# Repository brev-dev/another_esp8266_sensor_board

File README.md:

# Another ESP8266 Sensor Board

This repo contains build instructions for a multi-purpose esp8266 sensor device for home IoT projects. 

*Board V5, partially populated. Image generated in KiCad.*

## Contents

- [Introduction](https://github.com/brev-dev/another_esp8266_sensor_board#introduction)
  - [Example devices](https://github.com/brev-dev/another_esp8266_sensor_board#example-devices)
  - [Why use this board?](https://github.com/brev-dev/another_esp8266_sensor_board#why-use-this-board-and-not-insert-off-the-shelf-microcontroller-board-here)
- [Component discussion](https://github.com/brev-dev/another_esp8266_sensor_board#component-discussion)
  - [Power](https://github.com/brev-dev/another_esp8266_sensor_board#power)
  - [LDO regulator](https://github.com/brev-dev/another_esp8266_sensor_board#ldo-regulator)
  - [Electrical Noise](https://github.com/brev-dev/another_esp8266_sensor_board#electrical-noise)
  - [ESP8266](https://github.com/brev-dev/another_esp8266_sensor_board#esp8266)
  - [Voltage supervisor](https://github.com/brev-dev/another_esp8266_sensor_board#voltage-supervisor-optional-with-jumper-jp1)
  - [LORA module](https://github.com/brev-dev/another_esp8266_sensor_board#lora-rfwm95w-module)
  - [ADC connections](https://github.com/brev-dev/another_esp8266_sensor_board#adc-connections)
  - [Water pump, and connector](https://github.com/brev-dev/another_esp8266_sensor_board#water-pump-and-connector)
  - [Enclosure](https://github.com/brev-dev/another_esp8266_sensor_board#enclosure)
  - [Sensors](https://github.com/brev-dev/another_esp8266_sensor_board#sensors)
    - [Temperature, humidity, pressure (BME280)](https://github.com/brev-dev/another_esp8266_sensor_board#temperature-humidity-pressure-bme280)
    - [Lux (BH1750)](https://github.com/brev-dev/another_esp8266_sensor_board#lux-bh1750)
    - [CO<sub>2</sub> (MH-Z19C)](https://github.com/brev-dev/another_esp8266_sensor_board#co2-mh-z19c)
    - [Moisture](https://github.com/brev-dev/another_esp8266_sensor_board#moisture)
- [Design & fabrication](https://github.com/brev-dev/another_esp8266_sensor_board#design--fabrication)
- [Software](https://github.com/brev-dev/another_esp8266_sensor_board#software)
  - [Tasmota](https://github.com/brev-dev/another_esp8266_sensor_board#tasmota)
  - [Micropython](https://github.com/brev-dev/another_esp8266_sensor_board#micropython)
- [Home IOT setup](https://github.com/brev-dev/another_esp8266_sensor_board#home-iot-setup)
- [ToDo](https://github.com/brev-dev/another_esp8266_sensor_board#todo-could-be-done-not-necessarily-will-be-done)

## Introduction

This sensor board meets most of my home-automation hardware needs. It fits in a [cheap, widely-available enclosure](https://github.com/brev-dev/another_esp8266_sensor_board/blob/f84a305c095048d2f336beb286c9c32f08003d64/images/project_box.jpg) (no 3d printing required), and can be powered either by a Li-Ion battery (voltage-monitoring, charging, reverse-polarity, and protection circuitry included) or USB, with appropriate power sharing if the USB and battery are connected simultaneously. On the software side, I’ve kept things as high-level as possible: Tasmota for most usage scenarios; micropython where needed. Communication utilizes the MQTT protocol over Wi-Fi, or LORA (I use the board as both a [remote LORA sensor, and as a LORA-MQTT bridge](https://github.com/brev-dev/LORA_esp8266_sensor_MQTT_bridge/)).

The board is designed for the following [sensors](https://github.com/brev-dev/another_esp8266_sensor_board#sensors), as well as motor/pump control (for automatic plant watering). GPIO pins remain easily-accessible, so this board can also be used as the basis for many other sensors.

- [Temperature/Humidity/Pressure (BME280)](https://github.com/brev-dev/another_esp8266_sensor_board#temperaturehumiditypressure-bme280)
- [Lux (BH1750)](https://github.com/brev-dev/another_esp8266_sensor_board#lux-bh1750)
- [CO<sub>2</sub> (MH-Z19C)](https://github.com/brev-dev/another_esp8266_sensor_board#co2-mh-z19c)
- [Moisture](https://github.com/brev-dev/another_esp8266_sensor_board#moisture)

The use of an esp8266 comes with some limitations, specifically around available GPIO, and only one ADC port. This means that not all potential functionality is available at the same time. Yes, these limitations could be overcome either with a port splitter, or by utilizing a different microcontroller such as an ESP32; however part of the fun for me was seeing how much I could do with only the esp8266, and the end result fits all of my use-cases.

### Example devices

|  |  |
| --- | --- |
| *V4, with BME280 (temperature, pressure and humidity), BH1750 (lux) and moisture (via the audio plug) sensors. Equipped for watering pump (bottom right); not currently connected.* | *V5, with the BME280 and MH-Z19C (CO<sub>2</sub>) sensors* |

|  |
| --- |
| *A fresh delivery of V5 boards* |

### Why use this board, and not *\*insert-off-the-shelf-microcontroller-board-here\**?
You could (should?!) use something else. I initially designed this as a way to learn about IoT sensors and circuit design/fabrication. I’ve stuck with it because it provides several advantages over off-the-shelf boards:
1.	Convenient project-box fit without 3D printing
2.	No tangle of wires: most sensors are directly mounted to the board
3.	Theoretically better protection & stability (control over noise-suppression features, battery polarity protection, and voltage supervision). Of course, in practice this benefit is probably more than outweighed by my lack of board-design experience.

## Component Discussion

### Power

The board can be powered either directly from USB, or from a Li-Ion battery. Board V4 and earlier used micro-USB; V5 uses USB-C. The cutout on the left of the board is designed to accommodate a 1-cell 18650-battery case such as [this](https://github.com/brev-dev/another_esp8266_sensor_board/blob/980b60a9790c6bc3b052b28f8b95426f12ae9da2/images/18650_battery_case.jpg) ([purchase link](https://www.aliexpress.com/item/32993737904.html)). The battery connector is a 2-pin JST-PH (2mm pitch), but if you prefer, just solder the wires directly to the connectors.

If both battery and USB are connected simultaneously, a power-sharing circuit ensures that only the USB powers the board.
The battery is used in conjunction with a copy of the common 3-chip TP4056-based module for charging. There’s a switch provided if you’re not using a battery and want to bypass this circuitry (or if you don't want the battery to charge while USB is connected). The module includes protection for overcharge, over-discharge, overcurrent and short-circuit. Note that the overcurrent and short-circuit protection is bypassed for the rest of the board (not the battery) when USB is connected, and the power-sharing circuit is therefore active. 
The standard charging module doesn’t include battery-polarity protection, so I’ve also added that.

Battery voltage monitoring is available when either jumper JP5 (front) or JP6 (back) is bridged. This connects the positive battery terminal, through a voltage divider, to the esp's sole ADC pin. This connection is optional because the moisture sensor (and of course other sensors) also need access to the ADC. Due to this, it's clearly not possible to monitor both battery voltage and a soil moisture sensor at the same time with the V5 board.

*Notes*
- The FS8205 dual MOSFET chip comes in two package sizes. I chose the (slightly less common) SOT-23-6 variant because it's easier to hand-solder.
- Be aware that some AliExpress vendors are (I suspect accidentally) selling me4056 chips as tp4056. This chip has the same purpose but different pinout, so it won't work on the board. [Here's](https://github.com/brev-dev/another_esp8266_sensor_board/blob/a93f9e18d06ddcca5e1f6364de4ef48cf533c392/images/me4056.jpg) a bag of me4056's I received from one vendor (and was given a full refund when I finally worked-out what the problem was).
- As my 3-chip TP4056 charger footprint remains consistent with the widely-available modules, if you have one of those handy you can simply piggy-back it, rather than adding components directly to the board. [Here's](https://github.com/brev-dev/another_esp8266_sensor_board/blob/f170df5e5ed5a01450a450957b2c13060da18a92/images/tp4056_piggyback.jpg) an older example where I piggy-backed the charger circuit: just join the 6 corner pads. Note that the pictured module also comes with the alternative 8205A MOSFET package.
- I chose USB sockets that were as easy to hand-solder as possible, noting that only the power, not data, connectors are needed. For micro-USB you can find a [2-pin socket](https://github.com/brev-dev/another_esp8266_sensor_board/blob/e99d01fb7cc91dd79cf12d4cf2d8f64e2b0c8e33/datasheets/microUSB_socket_2pin.jpg) ([purchase link](https://www.aliexpress.com/item/33039304643.html)). I haven't found an equivalent for USB-C, but [this](https://github.com/brev-dev/another_esp8266_sensor_board/blob/e99d01fb7cc91dd79cf12d4cf2d8f64e2b0c8e33/datasheets/usbc_socket_6pin.webp) socket ([purchase link](https://www.aliexpress.com/item/4000011358933.html)) offers a smaller number of connectors (enough for USB2 data as well as power, I believe).
- If you only need a minimal USB-powered board, you can skip all of the charging, power sharing and reverse polarity components. Just add a USB socket (or connect directly to pads H5 (+5v) and H6 (ground), and bridge the two pads on diode footprint D2.

### LDO regulator

There’s a dizzying range of possible LDO ICs to choose from. I settled on the XC6203P332PR due to its relatively high current output, and low dropout voltage. Board V4 had footprints for two alternative regulators, which I was planning to test for stability, but these weren’t needed and were removed in V5. 
#### Tantalum capacitors
On PCB version 4 I paired two 1μF tantalum capacitors with the XC6203, per the [datasheet](https://github.com/brev-dev/another_esp8266_sensor_board/blob/86c8875968cf48237dee9fcda43d4448a1e4a00b/datasheets/XC6203.pdf). I had a capacitor fail on two of these boards after a few weeks of use, causing a short-circuit and lots of smoke (the boards were being USB-powered at the time). After reading tantalum horror-stories online, I decided to experiment with swapping them for ceramics on V5, and have experienced no further problems. I later discovered that the two failures were my fault: I fitted the parts in reverse! I’m sure there’s a good reason why the polarity-marker band on tantalums denotes the positive, while on aluminium capacitors and diodes it denotes the negative, but they tripped-up this newbie.

#### An aside: Cheap ESP-12F adaptor boards

Conveniently, the XC6203P332PR is also compatible with the[ white ESP-12F adaptor boards](https://github.com/brev-dev/another_esp8266_sensor_board/blob/0b8a2c9c500916e484b68a6f7c3c33d089ebb65e/images/esp-12f%20white%20adapter.jpg). It’s smaller than the provided footprint, but can still be soldered onto it with little trouble. Make sure you remove the central zero-ohm resistor on the front of the board if using a board-mounted regulator.

### Electrical Noise

I learned the hard way about the electrical-noise sensitivity of the ESP8266: on V3 of the board, it would reboot whenever the watering motor was activated. I overcame this in V4 with component repositioning (moving the motor to the far end away from the microcontroller), adding extra capacitors next to the motor connection, increasing power trace width vs signal traces, minimizing loops on the ground plane, and separating the motor ground-plane return path from the rest of the components.

### ESP8266
The board is designed for an ESP-12F. I tend to flash the chip in a [programmer board](https://github.com/brev-dev/another_esp8266_sensor_board/blob/0b8a2c9c500916e484b68a6f7c3c33d089ebb65e/images/esp-12f%20programmer.jpg) prior to soldering it on, just to check it's working.

When installed, it can be flashed in the normal way by connecting a USB-UART interface board to the appropriate pins.

#### Connection summary

| Pin# | Port | Board Connection | Resistor\* | 
| --- | --- | --- | --- | 
| 1 | RST | Reset button |  |
| 2 | ADC | ADC (moisture or battery)|  |
| 3 | EN | Chip enable | Supervisor, or E-PU |
| 4 | IO16 | DeepSleep |  |
| 5 | IO14 | I2C SCL, or SPI SCK |  |
| 6 | IO12 | Moisture VCC, or SPI SDO-MISO |  |
| 7 | IO13 | I2C SDA, or SPI MOSI |  |
| 8 | VCC |  |  | VCC |  |
| 15 | GND |  |  | GND |  |
| 16 | IO15 | LORA NSS | E-PD |
| 17 | IO2 | Onboard LED, & SPI SS |  |
| 18 | IO0 | Flash button | E-PU |
| 19 | IO4 | Mode switch (GND: use sleep) | E-PU |
| 20 | IO5 | Water pump, or LORA DIO | E-PD |
| 21 | RXD | CO<sub>2</sub> Tx |  |
| 22 | TXD | CO<sub>2</sub> Rx |  |

\* Resistor attached to pin: I:Internal, E:External, PU:Pull-Up, PD:Pull-Down

#### Deep sleep (optional with jumper JP2)

There seems to be some online [debates](https://www.esp8266.com/viewtopic.php?f=160&t=13625) about the optimal way to connect RST to GPIO16 in order to use the ESP8266’s DeepSleep functionality. I’ve erred on the side of caution and added a diode between the two.

### Voltage supervisor (optional with jumper JP1)

The ESP8266 is susceptible to brown-outs if the voltage is too low (a good explanation of this problem can be found [here](https://youtu.be/cKDv0aN67BY)). In conjunction with the non-instantaneous increase in voltage from the regulator when power is first applied, this can lead to boot problems. To protect against this, I’ve included an optional voltage supervisor ([TPS3839G33DBZ](https://github.com/brev-dev/another_esp8266_sensor_board/blob/4a8da56aba7b092c4e5784e14ad378a6c07b094b/datasheets/tps3839.pdf)) which will only set the chip-enable pin high when voltage is above an appropriate threshold. 
However, I’ve yet to notice brown-outs being a problem, so I sometimes skip this component.

### LORA (RFWM95W) module

*A pair of LORA-equipped devices in their enclosures*

Combining an esp8266 with a LORA module is a stretch when it comes to available gpio. This board is designed to work with SX1276 LORA modules ([example link](https://www.aliexpress.com/item/32984655636.html)), and leans heavily on the design from [here](https://github.com/hallard/WeMos-Lora), which minimizes needed ports by linking three of the LORA module's pins (DIO0, 1 and 2) to one esp8266 pin via three diodes (board footprints D9, D10 and D11 respectively). This DIO-sharing configuration needs special handling in software. However, for simple LORA communications only DIO0 is needed, so for my LORA boards to date I have bridged D9, and left D10 and D11 disconnected.

#### Antenna
For testing, you can directly solder the common helical-wire antennas (often included with the purchase of a module) directly to the module's antenna pin. Range will suck, though. For better range attach a higher-gain antenna (I use 5dbi antennas bought [here](https://www.aliexpress.com/item/32979875502.html)). I include an IPEX U.FL-R footprint at AE1. Alternatively, SMA edge-mounted connectors fit nicely on the edge of the board over footprint J5. These can be wired-up as follows (this example is using board V4, but the same will work for V5): [top](https://github.com/brev-dev/another_esp8266_sensor_board/blob/493c38c68af71970a35fda9a3fc562d0f8774722/images/antenna_top.jpg) and [bottom](https://github.com/brev-dev/another_esp8266_sensor_board/blob/493c38c68af71970a35fda9a3fc562d0f8774722/images/antenna_bottom.jpg).

*Notes*
- Remember to install capacitor C10 if you're adding a LORA module to the board.

### ADC Connections

A single ADC is available on the esp8266, with a measurement range from 0V to 1V. For measuring higher voltages, a [voltage divider](https://ohmslawcalculator.com/voltage-divider-calculator) is therefore needed. On board V5, the ADC can either be used for peripherals connected to the audio jack, or to monitor the battery voltage if either JP11 or JP5 is closed.

Connections via the audio jack go through a divider with R1=470 kΩ (component R7), R2=200 kΩ (component R8). This permits measurement of voltages up to 3.3V (3.3V is lowered to approximately 0.985V; calibrate the signal for higher accuracy).

The battery connection adds an additional 330 kΩ (component R10) resistor in series with component R7, leading to R1=800 kΩ. This increases the measurement range up to 5V.

#### The audio-style socket
I chose to use a 4-pole audio jack (model PJ313E) to connect the moisture sensors to the board. For now, only three of the four poles are connected; the fourth is a spare with an eye to future functionality. Starting from the base to the tip of the audio plug, the current connections are:

| Pole | Connection |
| --- | --- |
| 1 | GND |
| 2 | No connection |
| 3 | 3.3V (from GPIO12, via JP3) |
| 4 | To ADC via 3.3V voltage divider |

I've experienced one problem with my chosen socket (or maybe the combination of the socket and the plugs I use): by default, it's failing to make a connection to all four poles. This can be seen in the top image [here](https://github.com/brev-dev/another_esp8266_sensor_board/blob/e8318408b542502163760f25e8133f11a53af489/images/audio_socket_mod.jpg), where the deepest contact-pin (Pole 4) isn't deflected. To fix the problem, I snipped/filed-off the protruding plastic front part of the socket ([bottom image](https://github.com/brev-dev/another_esp8266_sensor_board/blob/e8318408b542502163760f25e8133f11a53af489/images/audio_socket_mod.jpg))

### Water pump, and connector
Small water pumps and the necessary flexible tubing are widely available. As discussed [above](https://github.com/brev-dev/another_esp8266_sensor_board/blob/main/README.md#electrical-noise), they're electrically-noisy buggers; hence why the connector for the pump is in the far corner of the board from the esp, and shielded behind two capacitors of its own. It's normally powered by gpio5, via an N-channel MOSFET, or can be manually operated with the optional button SW5.

For simplicity, and since the small pumps seem to be able to function over quite a wide voltage range, the pump is supplied with whatever voltage is currently powering the board (defined by the state of the power sharing circuitry): if USB is connected, it'll be 5V minus the forward voltage across diodes D2 and D8; if battery-powered, it'll be the battery voltage minus the D8 drop. In practice it really doesn't make much difference: slightly more water will be pumped during a given time when on USB vs battery-powered.

For the pump's board connection, there's a footprint for a DC-002 socket. I considered using a USB socket but decided that was misleading since the output voltage isn't always the 5V that one would expect from USB. On the board pictured above, I skipped the power-jack socket and simply connected a double pin-header socket instead.

### Enclosure

I chose [this project box](https://github.com/brev-dev/another_esp8266_sensor_board/blob/f84a305c095048d2f336beb286c9c32f08003d64/images/project_box.jpg) because it's cheap, widely-available, and just the right size for the pcb and an 18650 battery.

8mm M2.6 screws are needed to attach the board to the box, such as [these](https://www.aliexpress.com/item/4000108693024.html).

### Sensors

| Property | Module | Board Connection | Datasheet | Purchase Link\*|
| ---| --- | --- | :---: | --- |
| Temperature, pressure, humidity | BME280 | Direct (2.54mm headers) | [Link](https://github.com/brev-dev/another_esp8266_sensor_board/blob/e3f53c214705e32eaa9f90e711b66ee1d1c71691/datasheets/BST-BME280_DS001-11-844833.pdf) | |
|	Lux | BH1750 | Direct (2.00mm headers) | [Link](https://github.com/brev-dev/another_esp8266_sensor_board/blob/d842e8ac7ead9bd1a256e17d498e4c6692d75f80/datasheets/BH1750FVI.pdf) | [AliExpress](https://www.aliexpress.com/item/32983784786.html) |
|	CO<sub>2</sub> | MH-Z19C | Direct (2.54mm headers) | [Link](https://github.com/brev-dev/another_esp8266_sensor_board/blob/55dd2d41b445c80636574d447e5fac080cfa47e3/datasheets/mh-z19c-pins-type-co2-manual-ver1_0.pdf) | [AliExpress](https://www.aliexpress.com/item/4000586074848.html) |
| Moisture | “Capacitive soil moisture sensor V1.2” | Audio plug | [Link](https://github.com/brev-dev/another_esp8266_sensor_board/blob/e3f53c214705e32eaa9f90e711b66ee1d1c71691/datasheets/sen0193-humedad-de-suelos.pdf) (older version) | [AliExpress](https://www.aliexpress.com/item/32908693444.html) |

\**I've purchased from those links in the past, but they're provided with no guarantee. I also don't plan to update them when they inevitably expire.*

#### Temperature, humidity, pressure (BME280)

This is a very handy temperature, humidity and pressure sensor. With the sensor's current mount point, it sits partially outside of the enclosure. I find this convenient because I don't have to worry about airflow within the box. If the current geometry offends you, or you need a more robust device where the sensor won't risk getting damaged, consider a redesign on the connection point, or choose an alternative sensor with a built-in cage.

You might find that the soldered pins get in the way of closing the enclosure lid properly. If this is the case you can trim them prior to soldering, like I've done [here](https://github.com/brev-dev/another_esp8266_sensor_board/blob/7ec4fd718edccba7780aa4c0607bf689e7137857/images/bme280_trimmed_pins.jpg).

The sensor can communicate by I2C or SPI; most people seem to use I2C, for which you need to make no board alterations. If you want the SPI interface, close a [couple](https://github.com/brev-dev/another_esp8266_sensor_board/blob/bff7ac836695f352a52cb5e7e18f4aab712b4d77/images/rear_solder_bridges_bme_spi.jpg) of solder bridges on the rear to connect the additional pins. On board V5, one of these connections also powers the moisture sensor, so alterations would be needed if you want to run both the BME280 (with SPI interface) and a moisture sensor concurrently.

*Notes*
- The BME280 is reported to be a nicely precise sensor, but not always accurate. Specifically, the temperature sensor produces high readings (by up to a couple of degrees) due to the heat produced by the sensor itself when active. The level of this offset depends on how you run the sensor: if you only wake it up for readings, putting it to sleep inbetween, the offset is smaller than if you run it continually. However, since the offset appears consistent, you can easily calibrate it out post-measurement.
- Hey, when did this sensor become so expensive?! As of mid-2021, there's [apparently](https://forum.sensor.community/t/bme280-global-shortage/413) a global shortage which will hopefully end soon.
  - At the current prices, maybe it's worth stumping for the BME680 (like the BME280, with an additional VOC sensor). This looks as though it's pin-compatible for I2C. With SPI, you'd need to swap the two additional pins (which could be achieved with crossing links across solder bridges JP3 and JP4)
  - If cost is important, some projects are swapping-out the BME280 for an SHT31. This is also I2C, just no pressure sensor. I have no experience of this sensor, but it looks to be a simple swap-in.
  - There is also the BMP280. It's like the BME280, but without pressure sensor.

#### Lux (BH1750)
This is a simple and reliable photodiode, combined with an I2C interface. You can buy it in various form-factors, with the light-ball version being particularly convenient for our purposes. [Trim-down the plastic parts of the built-in connector](https://github.com/brev-dev/another_esp8266_sensor_board/blob/7ec4fd718edccba7780aa4c0607bf689e7137857/images/bh1750_trimmed.jpg), and this can now plug directly into a standard 2mm-pitch pin header, as included on board V5. The light ball can be popped off the sensor and directly mounted into the [top of the enclosure](https://github.com/brev-dev/another_esp8266_sensor_board/blob/5aa659a7452a0eb0ab53f27bc85ff3bf4364177d/images/bh1750_case.jpg).

*Notes*
- This sensor can't be mounted at the same time as the MH-Z19C below, for purely physical reasons. There are no port conflicts, so they'll happily operate concurrently if you make PCB changes, or connect one or other with an extension cable.

#### CO<sub>2</sub> (MH-Z19C)

This is the priciest sensor I use, but I think it's worth it vs the cheaper VOC alternatives. It communicates over the UART bus (so esp8266 pins Rx and Tx). You therefore want to ensure the sensor isn't connected if you're trying to flash the ESP or use its serial interface.

To use the MH-Z19C on the board V5, you need to [connect two solder bridges on the rear](https://github.com/brev-dev/another_esp8266_sensor_board/blob/bff7ac836695f352a52cb5e7e18f4aab712b4d77/images/rear_solder_bridges_CO2.jpg). In hindsight I can't think of a good use-case when you wouldn't want those bridged, so I'll probably just swap the pads out for continuous traces on any future version.

*Notes*
- As usual, Andreas Spiess has a good [video](https://youtu.be/FL0L-nic9Vw) on the topic.
- This sensor is powered by 5V, not 3.3V like most of the other components. For this reason, you should only use it when running from USB power (the board has no step-up capabilities for getting 5V from the battery, and since the MH-Z19C is designed to be continuously-powered, it'd probably be a big battery drain anyway).
- As currently wired (board V5) the sensor will continue running even if the board's power switch is turned to off. This is because it's connected earlier in the power circuit: I haven't tested whether it will run reliably on the lower voltage that'll be present after the power-sharing doide D2.
- As noted above, cannot be mounted on the board at the same time as a BH1750.
- When I first started this project, the manufacturer was in the process of changing from Z19B to the newer Z19C sensors and they were hard to come by. The situation seems to have improved. Choose a Z19C if available (better performance, apparently), and select the one with pins if you plan to directly mount it into the two corresponding board sockets.

#### Moisture

In order to stop the moisture sensor running constantly and draining the battery, it's powered directly by gpio12. Bridge the right pad of JP3 to the centre pad to make that connection. It doesn't draw much current, so I've had no problems directly powering the sensor directly from a gpio pin. If it turned out to be a brown-out/stability issue in the future, this connection would need to be replaced by a MOSFET.

## Design & Fabrication

The board was designed in [KiCad](https://www.kicad.org/), and manufactured by [JLCPCB](https://jlcpcb.com). KiCad files and the information required by JLCPCB are provided in the board_v* directories.

Please be understanding with [the schematic](https://github.com/brev-dev/another_esp8266_sensor_board/blob/9ac3180b3b5d9ca07b58c377a639be6fb8d97420/board_v5/schematic_v5.pdf); I know it's ugly and desperately in need of splitting into multiple parts. Remember, this is my first PCB design!

*Board V5 layout*

## Software

For convenience, I use Tasmota for all devices where possible. Tasmota can't handle LORA, so for these devices I use micropython.

### Tasmota

[Web install link](https://tasmota.github.io/install/)

Make sure you install the "sensors" version of the tasmota image.

Here are some Tasmota screenshots from the V4 device [pictured](https://github.com/brev-dev/another_esp8266_sensor_board/blob/f81dc558d201dd6b186f64b55d8d96105131c601/images/example_board_v4.jpg) at the top of this readme.

  |  

Here are the main settings I changed from their default in the control interface. Read about these and other settings [here](https://tasmota.github.io/docs/Commands/).

- PulseTime1 12 (for the modules configured for watering on Relay1, choose your watering length here. This example defines the watering length as 1 second)
- DeepSleepTime 120 (defines the time between readings in seconds if you are using DeepSleep)
- SetOption65 1 (disables device recovery using [fast power cycle detection](https://tasmota.github.io/docs/Device-Recovery/#fast-power-cycle-device-recovery). Instead, the device can be reset to defaults by pressing the flash button (GPIO0) for 40 seconds.
- TelePeriod 120 (seconds between MQTT reports - the default of 300seconds is a bit long for some of the environmental sensors)
- SerialLog 0 (only for things that use the serial port, such as the [433Mhz MQTT gateway](https://tasmota.github.io/docs/devices/Sonoff-RF-Bridge-433/#flash-tasmota): disable serial logging so it doesn't interfere with access to the module)
- [SetOption13 1](https://tasmota.github.io/docs/Commands/#setoption13) (disable double-press for faster single-press)
- [WifiConfig 4](https://tasmota.github.io/docs/Commands/#wi-fi) (test each AP in turn if WiFi signal is lost, rather than setting WiFi Manager running at 192.168.1.4)

*Notes*
- I leave the analog signal reported as raw values, and then calibrate this later (in NodeRed). I believe you could also setup the calibration in Tasmota's control interface. On the example device, the moisture sensor gave a reading of 605 when dry and 282 when submerged in water. An Analog0 reading of 482 therefore corresponds to a moisture level of 38%.
- When configured as above, power is sent to the moisture sensor when Toggle 2 is set to ON. I expected this state to survive reboots and deep sleep because Tasmota's [PowerOnState](https://tasmota.github.io/docs/PowerOnState/) is set to 3. Unfortunately this isn't happening, so the moisture sensor isn't working by default when the device wakes. There are a few ways to avoid this problem:
   1. It's probably fixable within Tasmota's other options (maybe SetOption63?)
   2. Add a retained MQTT `POWER2 ON` command 
   3. (What I'm currently doing) set GPIO12 (the pin powering the moisture sensor) to `Output Hi` rather than `Relay 2`. It'll then be set high early in Tasmota's boot process, and still switch off when the microcontroller goes into deep sleep.
- Tasmota can probably also be configured to carry-out the watering function directly, when the moisture goes below a certain level. However, I do this in NodeRed, broadcasting the command to the device by MQTT.

### MicroPython

Look here for my LORA micropython software and instructions: https://github.com/brev-dev/LORA_esp8266_sensor_MQTT_bridge.

## Home IoT Setup

Although not covered by this repo, here are some quick notes on where these devices sit in my full home setup.

My home setup is designed to achieve these goals:
1. Automatic temperature control
2. Plant auto-watering
3. Informing other manual actions, such as ventilation, and some manual plant watering
4. Purely informational.

To enable temperature control in each room, the radiators are plugged into Tasmotized esp8285 smart plugs.

The "hub" is a Raspberry Pi 4 equipped with Mosquitto, NodeRed, InfluxDB, and Grafana. My NodeRed flows could probably be simplified by replacing much of it with, for example, HomeAssistant, but I haven't looked into that. The combination of InfluxDB and Grafana is used to store and visualize the historical data (examples below), along with the "MQTT Dash" app on our phones to monitor the current status and change temperature and moisture trigger levels. The rpi software stack utilizes Docker and [IOTStack](https://github.com/SensorsIot/IOTstack) for ease of configuration and maintenance. Andreas Spiess has some great videos on the topic, including: [#255](https://youtu.be/JdV4x925au0), [#295](https://youtu.be/a6mjt8tWUws), and [#352](https://youtu.be/KJRMjUzlHI8).

## ToDo (_could_ be done; not necessarily _will_ be done!)
- Bugfix: on/off labels are reversed on the Supervisor silkscreen on back of board. The labels on the front are correct
- Tidy-up the schematic
- Increase R12 to 10k (or even as high as 33k) to reduce the ferocity of green LED5
- Increase length of USB-C pin solder pads
- Add optional battery-polarity-protection bypass route (short pins 2 & 3 of Q1), or remove this additional circuitry
- Change position of, or rotate, Q4 (really hard to solder when SW1 is present)
- Round corners of board and cutout esp antenna area
- Remove (and join) JP8 and JP9, the jumpers to the Rx and Tx ports on the CO<sub>2</sub> sensor
- Optionally override the sleep mode switch when plugged into external power (such as the second example [here](https://tasmota.github.io/docs/DeepSleep/#using-a-switch)).
- Add UART-USB interface (e.g. CP2104)
- Convert board to esp32 (potentially the new esp32-c3f, as it's footprint-compatible?)
  - Wire-up extra GPIO
  - Wire-up extra analog ports
    - Dedicated battery-monitoring port
    - Additional moisture-sensor ports
  - Built-in USB JTAG interface
- Add a separately-powered RTC to improve deep-sleep battery drain.

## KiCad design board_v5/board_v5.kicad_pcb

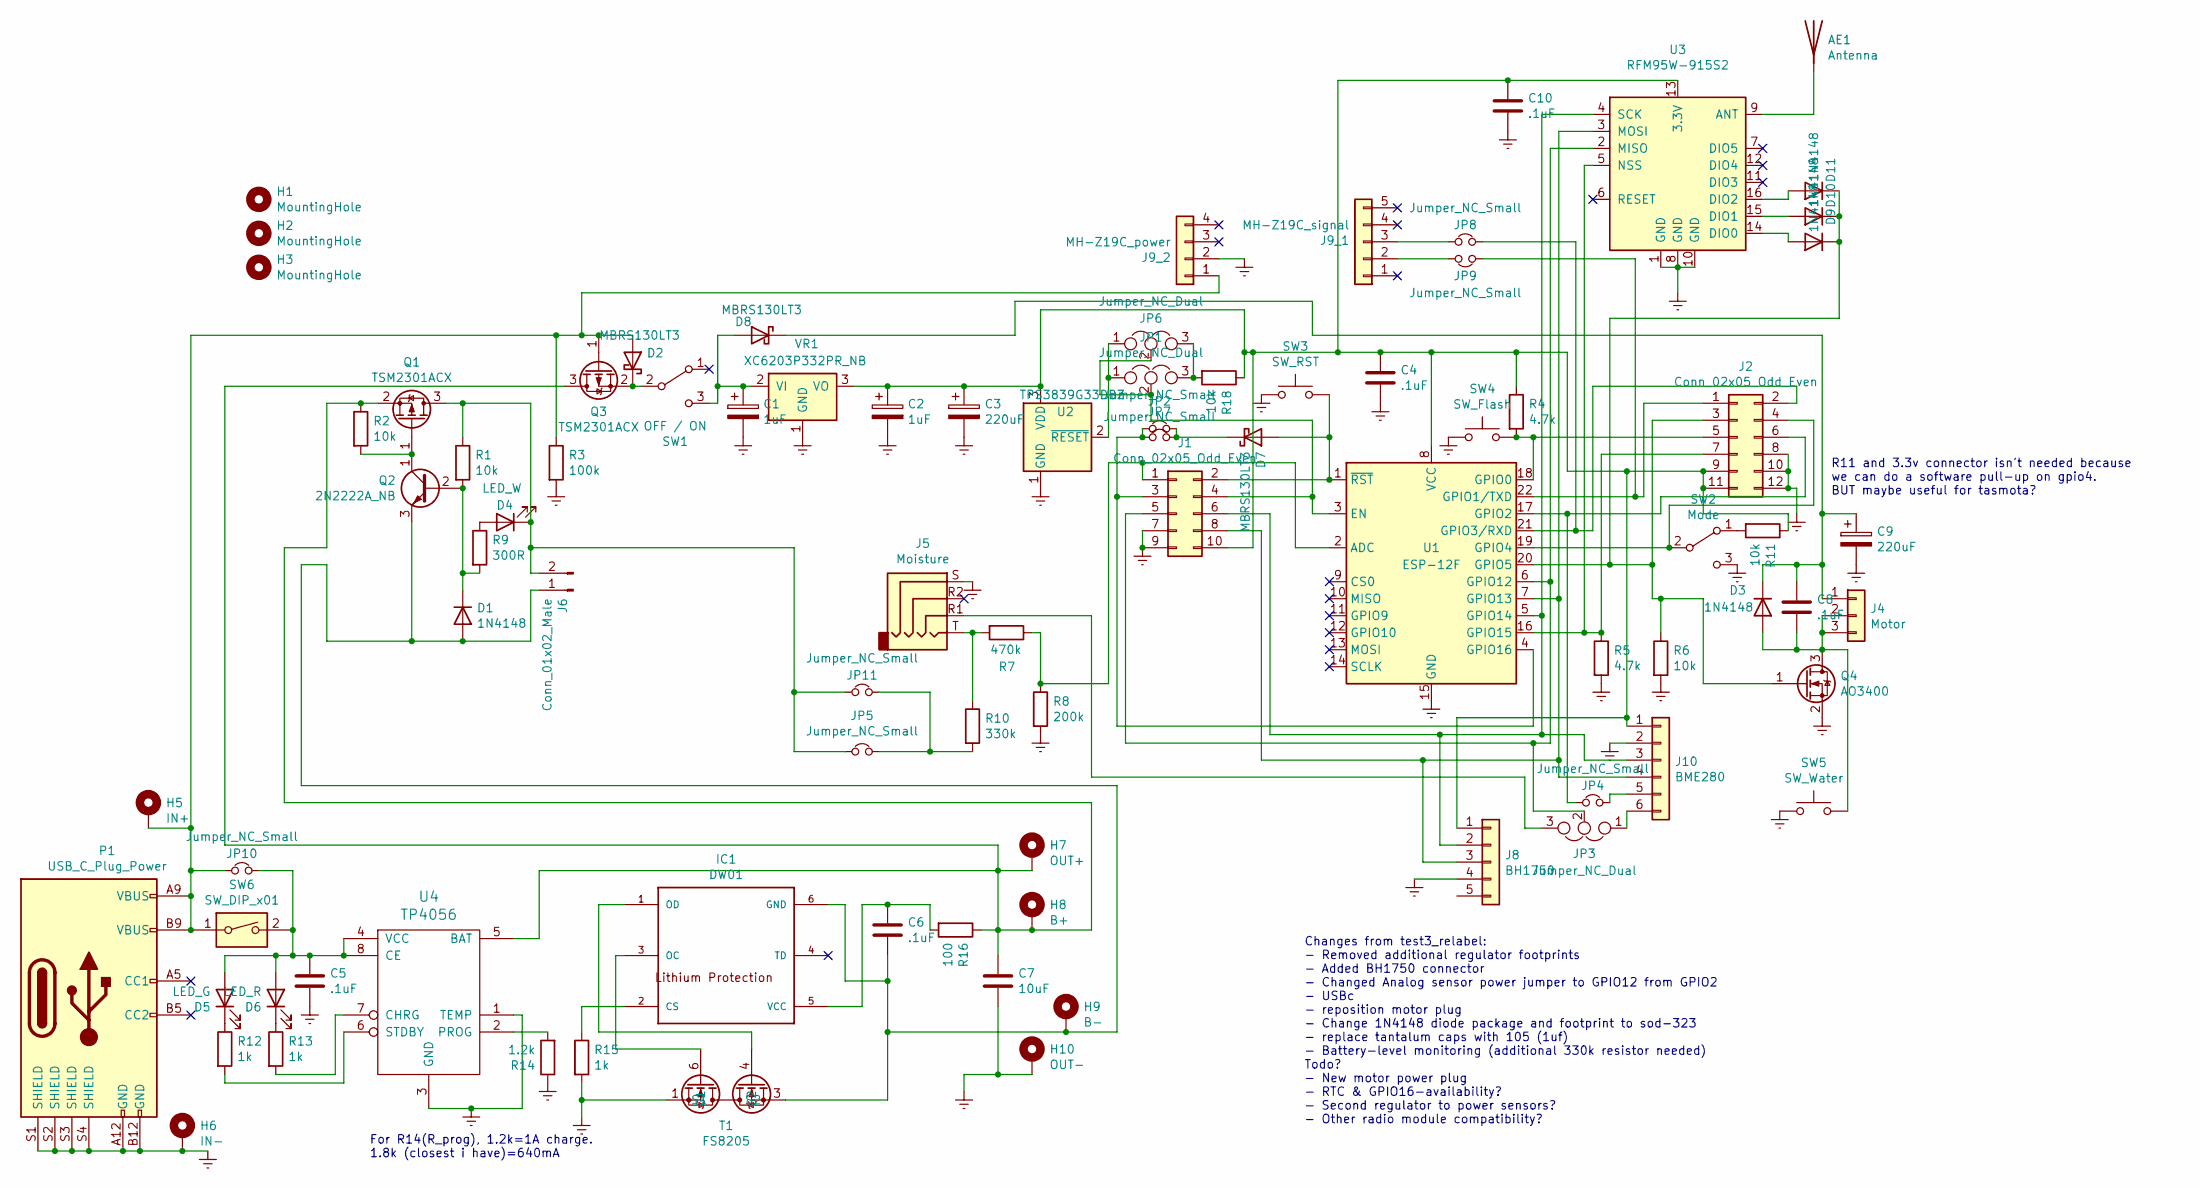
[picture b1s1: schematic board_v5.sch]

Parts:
AE1: Antenna; U.FL_Molex_MCRF_73412-0110_Vertical
C1, C2: 1uF; C_0805_2012Metric_Pad1.15x1.40mm_HandSolder
C3: 220uF; CP_Elec_6.3x5.4
C4, C5, C6, C8, C10: .1uF; C_0805_2012Metric_Pad1.15x1.40mm_HandSolder
C7: 10uF; C_0805_2012Metric_Pad1.15x1.40mm_HandSolder
C9: 220uF; CP_Radial_D5.0mm_P2.00mm
D1, D3, D9, D10, D11: 1N4148; D_SOD-323_HandSoldering
D2, D7, D8: MBRS130LT3; D_SMB
D4: LED_W; LED_0805_2012Metric_Pad1.15x1.40mm_HandSolder
D5: LED_G; LED_0805_2012Metric_Pad1.15x1.40mm_HandSolder
D6: LED_R; LED_0805_2012Metric_Pad1.15x1.40mm_HandSolder
H1, H2, H3: MountingHole; MountingHole_2.5mm
H5: IN+; TP4056_1pad_sm
H6: IN-; TP4056_1pad_sm
H7: OUT+; TP4056_1pad_sm
H8: B+; TP4056_1pad_sm
H9: B-; TP4056_1pad_sm
H10: OUT-; TP4056_1pad_sm
IC1: DW01; SOT-23-6_Handsoldering
J1: Conn_02x05_Odd_Even; PinHeader_2x05_P2.54mm_Vertical
J2: Conn_02x05_Odd_Even; PinHeader_2x06_P2.54mm_Vertical
J4: Motor; DC002_C12568
J5: Moisture; Jack_3.5mm_PJ313e_NB
J6: Conn_01x02_Male; JST_PH_B2B-PH-K_1x02_P2.00mm_Vertical
J8: BH1750; PinHeader_1x05_P2.00mm_Vertical
J9_1: MH-Z19C_signal; PinHeader_1x05_P2.54mm_Vertical
J9_2: MH-Z19C_power; PinHeader_1x04_P2.54mm_Vertical
J10: BME280; PinHeader_1x06_P2.54mm_Vertical
JP1: Jumper_NC_Dual; PinHeader_1x03_P2.54mm_Vertical
JP2, JP5: Jumper_NC_Small; PinHeader_1x02_P2.54mm_Vertical
JP3, JP6: Jumper_NC_Dual; SolderJumper-3_P1.3mm_Open_RoundedPad1.0x1.5mm
JP4, JP7, JP8, JP9, JP10, JP11: Jumper_NC_Small; SolderJumper-2_P1.3mm_Open_RoundedPad1.0x1.5mm
P1: USB_C_Plug_Power; usb_type-c_6-pin
Q1, Q3: TSM2301ACX; SOT-23_Handsoldering
Q2: 2N2222A_NB; SOT-23_Handsoldering
Q4: AO3400; SOT-23_Handsoldering
R1, R2, R6, R11, R18: 10k; R_0805_2012Metric_Pad1.15x1.40mm_HandSolder
R3: 100k; R_0805_2012Metric_Pad1.15x1.40mm_HandSolder
R4, R5: 4.7k; R_0805_2012Metric_Pad1.15x1.40mm_HandSolder
R7: 470k; R_0805_2012Metric_Pad1.15x1.40mm_HandSolder
R8: 200k; R_0805_2012Metric_Pad1.15x1.40mm_HandSolder
R9: 300R; R_0805_2012Metric_Pad1.15x1.40mm_HandSolder
R10: 330k; R_0805_2012Metric_Pad1.15x1.40mm_HandSolder
R12, R13, R15: 1k; R_0805_2012Metric_Pad1.15x1.40mm_HandSolder
R14: 1.2k; R_0805_2012Metric_Pad1.15x1.40mm_HandSolder
R16: 100; R_0805_2012Metric_Pad1.15x1.40mm_HandSolder
SW1: OFF / ON; SS-12F23
SW2: Mode; SS-12F23
SW3: SW_RST; SW_PUSH_6mm_THT_2pin_V2
SW4: SW_Flash; SW_PUSH_6mm_THT_2pin_V2
SW5: SW_Water; SW_Tactile_SPST_Angled_NB
SW6: SW_DIP_x01; SW_DIP_SPSTx01_Slide_6.7x4.1mm_W7.62mm_P2.54mm_LowProfile
T1: FS8205; SOT-23-6_Handsoldering
U1: ESP-12F; ESP-12E
U2: TPS3839G33DBZ; SOT-23_Handsoldering
U3: RFM95W-915S2; HOPERF_RFM9XW_SMD
U4: TP4056; TP4056_SOIC-8
VR1: XC6203P332PR_NB; SOT-89-3_Handsoldering

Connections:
Earth: C1.2, C2.2, C3.2, C4.2, C5.2, C7.2, C9.2, C10.2, H6.1, H10.1, J1.7, J1.9, J2.8, J2.10, J2.12, J5.S, J8.4, J9_2.2, J10.2, P1.A12 (GND), P1.B12 (GND), P1.S1 (SHIELD), P1.S2 (SHIELD), P1.S3 (SHIELD), P1.S4 (SHIELD), Q4.2 (S), R3.2, R5.2, R6.2, R8.2, R14.1, R15.2, SW2.3 (C), SW3.1, SW4.1, SW5.1, T1.1 (S1), U1.15 (GND), U2.1 (GND), U3.1 (GND), U3.8 (GND), U3.10 (GND), U4.1 (TEMP), U4.3 (GND), VR1.1 (GND)
unnamed: AE1.1, U3.9 (ANT)
unnamed: C1.1, D8.2 (A), SW1.3 (C), VR1.2 (VI)
unnamed: C5.1, D5.2 (A), D6.2 (A), JP10.2, SW6.2, U4.4 (VCC), U4.8 (CE)
unnamed: C6.1, IC1.5 (VCC), R16.2
unnamed: C6.2, D1.2 (A), H9.1, IC1.6 (GND), J6.1, Q2.3 (E), T1.3 (S2)
unnamed: C7.1, H7.1, H8.1, Q1.2 (S), Q3.3 (D), R2.1, R16.1, U4.5 (BAT)
unnamed: C8.1, C9.1, D3.1 (K), D8.1 (K), J4.1
unnamed: C8.2, D3.2 (A), J4.2, J4.3, Q4.3 (D), SW5.2
unnamed: C2.1, C3.1, C4.1, C10.1, J1.10, J2.9, J2.11, J8.1, J10.1, R4.1, R11.1, R18.1, U1.8 (VCC), U2.3 (VDD), U3.13 (3.3V), VR1.3 (VO)
unnamed: D1.1 (K), Q2.2 (B), R1.2, R9.2
unnamed: D2.1 (K), Q3.2 (S), SW1.2 (B)
unnamed: D2.2 (A), H5.1, J9_2.1, JP10.1, P1.A9 (VBUS), P1.B9 (VBUS), Q3.1 (G), R3.1, SW6.1
unnamed: D4.1 (K), J6.2, JP5.1, JP11.1, Q1.3 (D), R1.1
unnamed: D4.2 (A), R9.1
unnamed: D5.1 (K), R12.1
unnamed: D6.1 (K), R13.1
unnamed: D7.1 (K), JP2.2, JP7.2
unnamed: D7.2 (A), J1.2, SW3.2, U1.1 (~RST)
unnamed: D9.2 (A), U3.14 (DIO0)
unnamed: D9.1 (K), D10.1 (K), D11.1 (K), J2.3, Q4.1 (G), R6.1, U1.20 (GPIO5)
unnamed: D10.2 (A), U3.15 (DIO1)
unnamed: D11.2 (A), U3.16 (DIO2)
unnamed: IC1.1 (OD), T1.4 (G2)
unnamed: IC1.2 (CS), R15.1
unnamed: IC1.3 (OC), T1.6 (G1)
unnamed: J1.1, R7.1, R8.1, U1.2 (ADC)
unnamed: J1.3, JP2.1, JP7.1, U1.4 (GPIO16)
unnamed: J1.4, JP1.2, JP6.2, U1.3 (EN)
unnamed: J1.5, JP3.2, U1.6 (GPIO12), U3.2 (MISO)
unnamed: J1.6, J8.2, J10.3, U1.5 (GPIO14), U3.4 (SCK)
unnamed: J1.8, J8.3, J10.4, U1.7 (GPIO13), U3.3 (MOSI)
unnamed: J2.1, JP9.1, U1.22 (GPIO1/TXD)
unnamed: J2.2, JP8.2, U1.21 (GPIO3/RXD)
unnamed: J2.4, SW2.2 (B), U1.19 (GPIO4)
unnamed: J2.5, R4.2, SW4.2, U1.18 (GPIO0)
unnamed: J2.6, JP4.1, U1.17 (GPIO2)
unnamed: J2.7, R5.1, U1.16 (GPIO15), U3.5 (NSS)
unnamed: J5.R1, JP3.3
unnamed: J5.T, R7.2, R10.1
unnamed: J9_1.2, JP9.2
unnamed: J9_1.3, JP8.1
unnamed: J10.5, JP4.2
unnamed: J10.6, JP3.1
unnamed: JP1.1, JP6.1, U2.2 (~RESET)
unnamed: JP1.3, JP6.3, R18.2
unnamed: JP5.2, JP11.2, R10.2
unnamed: Q1.1 (G), Q2.1 (C), R2.2
unnamed: R11.2, SW2.1 (A)
unnamed: R12.2, U4.6 (STDBY)
unnamed: R13.2, U4.7 (CHRG)
unnamed: R14.2, U4.2 (PROG)

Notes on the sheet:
R11 and 3.3v connector isn't needed because we can do a software pull-up on gpio4. BUT maybe useful for tasmota?
For R14(R_prog), 1.2k=1A charge. 1.8k (closest i have)=640mA
Changes from test3_relabel: - Removed additional regulator footprints - Added BH1750 connector - Changed Analog sensor power jumper to GPIO12 from GPIO2 - USBc - reposition motor plug - Change 1N4148 diode package and footprint to sod-323 - replace tantalum caps with 105 (1uf) - Battery-level monit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

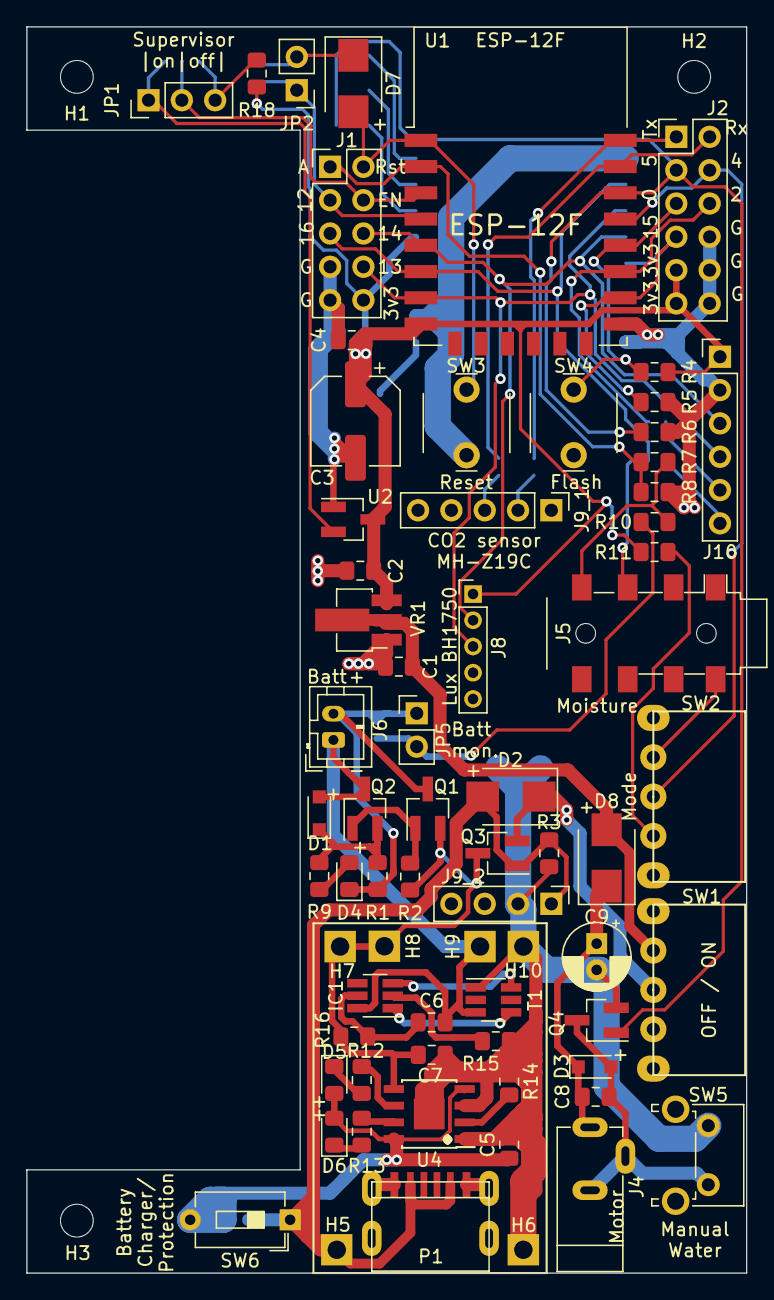
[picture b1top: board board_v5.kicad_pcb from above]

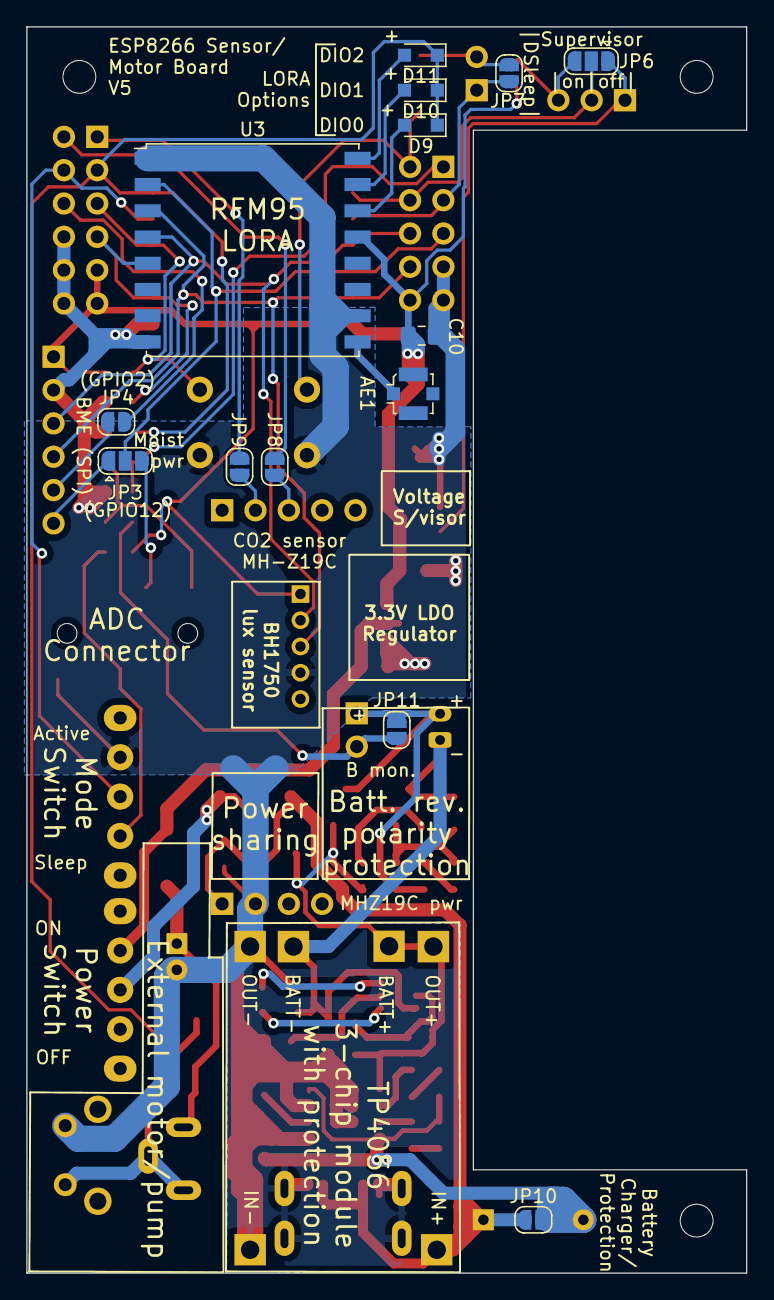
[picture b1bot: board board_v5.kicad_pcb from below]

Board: 2 copper layers, 54.9 x 95.0 mm, 86 parts (14 on the bottom side), 52 nets.

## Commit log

2021-08-12 Create LICENSE
